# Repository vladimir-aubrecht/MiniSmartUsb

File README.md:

# MiniSmartUsb
Small usb socket with smart home integration.

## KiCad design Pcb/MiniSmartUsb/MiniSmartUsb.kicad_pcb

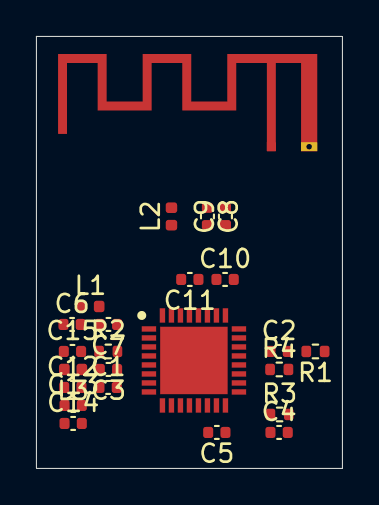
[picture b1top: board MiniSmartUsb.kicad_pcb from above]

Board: 2 copper layers, 17.0 x 24.0 mm, 24 parts (0 on the bottom side), 12 nets, no tracks yet.

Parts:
AE1: Antenna_Dipole; Texas_SWRA117D_2.4GHz_Left
C1, C2, C4, C5, C13, C15: 0.1 uF; C_0402_1005Metric
C3, C11, C12: 1 uF; C_0402_1005Metric
C6, C7: 1.5 pF; C_0402_1005Metric
C8, C9: TBD; C_0402_1005Metric
C10: 10 nF; C_0402_1005Metric
C14: 10 uF; C_0402_1005Metric
IC1: ESP32-C6FH4; QFN50P500X500X90-33N
L1: 2.7 nH; L_0402_1005Metric
L2: 24 nH; L_0402_1005Metric
L3: 2 nH; L_0402_1005Metric
R1, R2, R3, R4: 10 kOhm; R_0402_1005Metric

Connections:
GNDREF: AE1.1, C1.2, C2.2, C3.2, C4.2, C5.2, C6.2, C7.2, C8.2, C9.2, C10.2, C11.2, C12.2, C13.2, C14.2, C15.2, IC1.33 (GND)
unnamed: AE1.2, C6.1, L1.1
unnamed: C7.1, IC1.1 (ANT), L1.2
unnamed: C3.1, IC1.4 (CHIP_PU), R2.2
unnamed: C5.1, IC1.16 (GPIO12)
unnamed: C4.1, IC1.17 (GPIO13), R3.1
unnamed: IC1.19 (GPIO15), R1.2, R4.2
unnamed: C1.1, C2.1, C10.1, C11.1, C12.1, C13.1, C14.1, IC1.5 (VDDPST1), IC1.20 (VDDPST2), IC1.29 (VDDA1), IC1.32 (VDDA2), L3.1, R2.1, R3.2, R4.1
unnamed: C15.1, IC1.2 (VDDA3P3_1), IC1.3 (VDDA3P3_2), L3.2
unnamed: C9.1, IC1.30 (XTAL_N)
unnamed: IC1.31 (XTAL_P), L2.1
unnamed: C8.1, L2.2

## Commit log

2024-03-09 First draft
